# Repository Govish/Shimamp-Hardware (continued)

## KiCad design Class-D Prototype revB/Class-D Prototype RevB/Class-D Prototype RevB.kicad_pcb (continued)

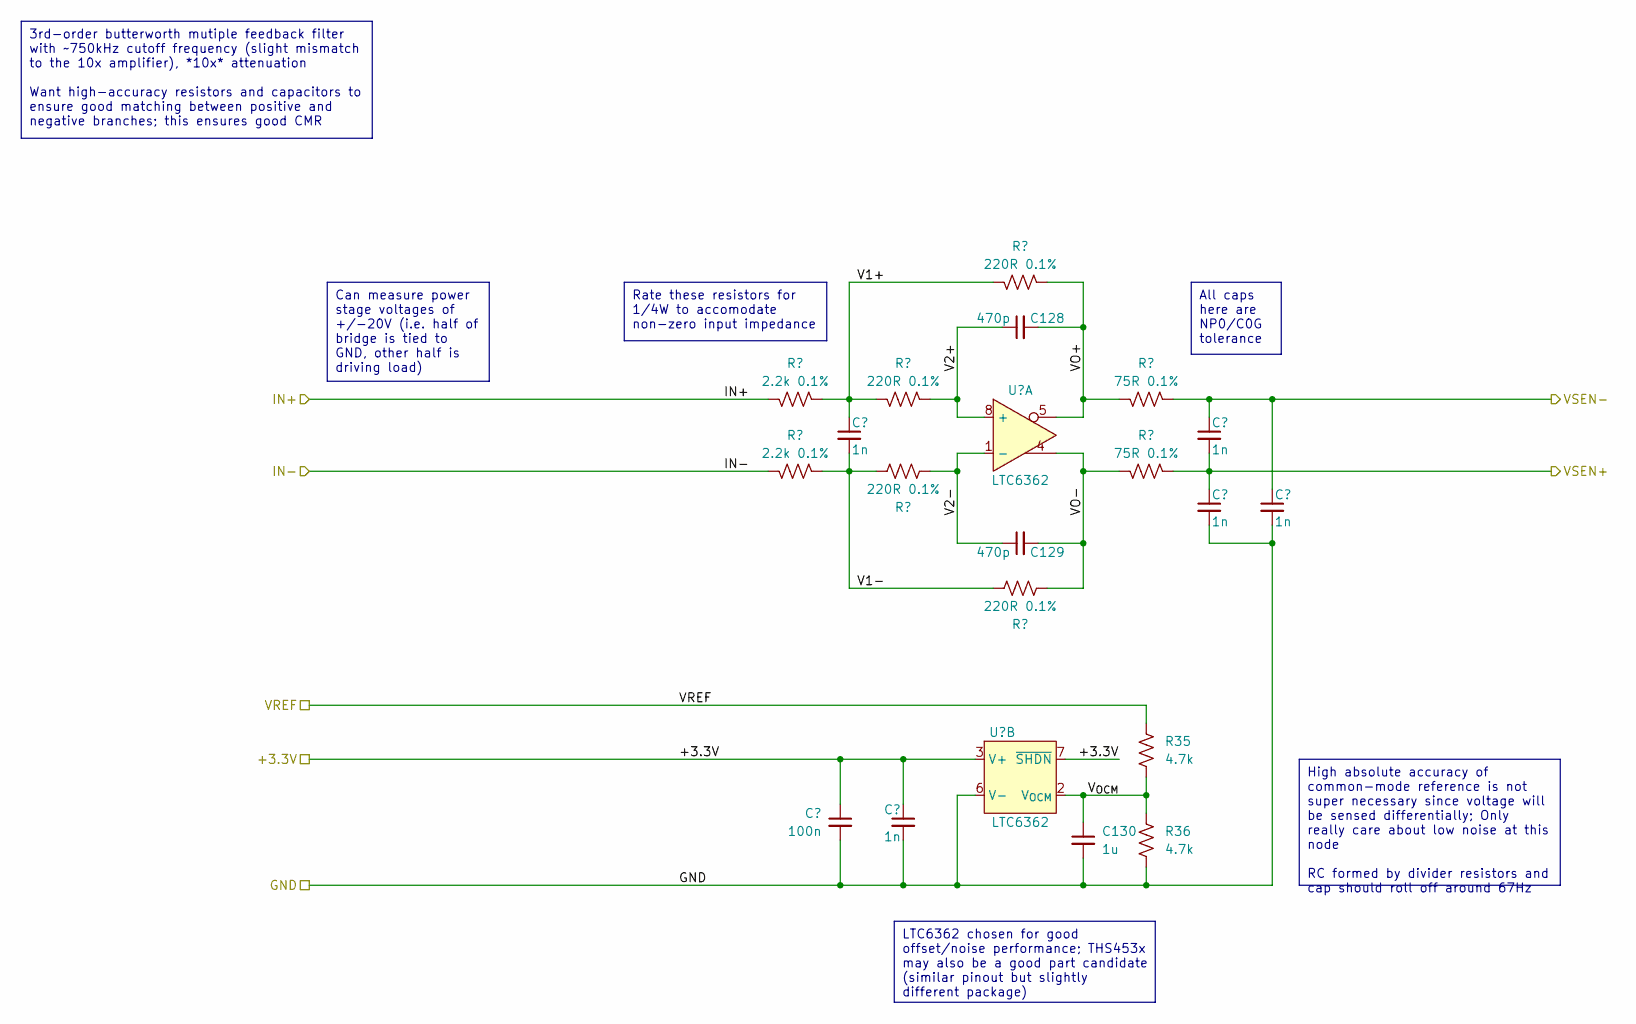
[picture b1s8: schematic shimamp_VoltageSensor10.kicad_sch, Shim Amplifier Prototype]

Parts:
C125: 100n; C_0603_1608Metric_Pad1.08x0.95mm_HandSolder; Part Number CL10B104KB8NNWC
C126, C127, C131, C132, C133: 1n; C_0603_1608Metric_Pad1.08x0.95mm_HandSolder; Part Number CL10B102KB8NNNC
C128, C129: 470p; C_0603_1608Metric_Pad1.08x0.95mm_HandSolder; Part Number GCM1885C2A471FA16D
C130: 1u; C_0805_2012Metric_Pad1.18x1.45mm_HandSolder; Part Number CL21B105KBFNNNG
R27, R28: 2.2k 0.1%; R_1206_3216Metric_Pad1.30x1.75mm_HandSolder; Part Number RN73R2BTTD2201B25
R29, R30, R31, R32: 220R 0.1%; R_0603_1608Metric_Pad0.98x0.95mm_HandSolder; Part Number RN73R1JTTD2200B25
R33, R34: 75R 0.1%; R_0603_1608Metric_Pad0.98x0.95mm_HandSolder; Part Number RN73R1JTTD75R0B25
R35, R36: 4.7k; R_0603_1608Metric_Pad0.98x0.95mm_HandSolder; Part Number RMCF0603FT4K70
U6: LTC6362; MSOP-8_3x3mm_P0.65mm; Part Number LTC6362CMS8#TRPBF

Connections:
+3.3V: C125.1, C127.1, U6.3 (V+), U6.7 (~SHDN); also elsewhere on the board
/Output Sensor/IN+: R27.2; also elsewhere on the board
/Output Sensor/IN-: R28.2; also elsewhere on the board
/Output Sensor/Voltage Sensor 10x/V1+: C126.1, R27.1, R29.2, R31.2
/Output Sensor/Voltage Sensor 10x/V1-: C126.2, R28.1, R30.2, R32.2
/Output Sensor/Voltage Sensor 10x/V2+: C128.1, R29.1, U6.8 (+)
/Output Sensor/Voltage Sensor 10x/V2-: C129.1, R30.1, U6.1 (-)
/Output Sensor/Voltage Sensor 10x/VO+: C128.2, R31.1, R33.2, U6.5
/Output Sensor/Voltage Sensor 10x/VO-: C129.2, R32.1, R34.2, U6.4
/Output Sensor/Voltage Sensor 10x/V_{OCM}: C130.1, R35.2, R36.1, U6.2 (V_{OCM})
/VSEN10x+: C131.2, C132.1, R34.1; also elsewhere on the board
/VSEN10x-: C131.1, C133.1, R33.1; also elsewhere on the board
GND: C125.2, C127.2, C130.2, C132.2, C133.2, R36.2, U6.6 (V-); also elsewhere on the board
V_{REF}: R35.1; also elsewhere on the board

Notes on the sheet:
LTC6362 chosen for good offset/noise performance; THS453x may also be a good part candidate (similar pinout but slightly different package)
3rd-order butterworth mutiple feedback filter with ~750kHz cutoff frequency (slight mismatch to the 10x amplifier), *10x* attenuation Want high-accuracy resistors and capacitors to ensure good matching between positive and negative branches; this ensures good CMR
All caps here are NP0/C0G tolerance
Rate these resistors for 1/4W to accomodate non-zero input impedance
Can measure power stage voltages of +/-20V (i.e. half of bridge is tied to GND, other half is driving load)
High absolute accuracy of common-mode reference is not super necessary since voltage will be sensed differentially; Only really care about low noise at this node RC formed by divider resistors and cap should roll off around 67Hz

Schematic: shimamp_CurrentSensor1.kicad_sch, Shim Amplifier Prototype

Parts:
C146, C148: 1n; C_0603_1608Metric_Pad1.08x0.95mm_HandSolder; Part Number CL10B102KB8NNNC
C147: 100n; C_0603_1608Metric_Pad1.08x0.95mm_HandSolder; Part Number CL10B104KB8NNWC
R48: 750R; R_0603_1608Metric_Pad0.98x0.95mm_HandSolder; Part Number RMCF0603FT750R
U9: INA241A1; SOT-23-8_Handsoldering; Part Number INA241A1IDDFR

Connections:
+3.3V: C147.1, U9.6 (VS); also elsewhere on the board
/ISEN1x: C148.1, R48.1; also elsewhere on the board
/Output Sensor/IS+: U9.8 (+); also elsewhere on the board
/Output Sensor/IS-: U9.1 (-); also elsewhere on the board
GND: C146.2, C147.2, C148.2, U9.2 (GND), U9.4 (GND), U9.7 (REF1); also elsewhere on the board
unnamed: R48.2, U9.5
V_{REF}: C146.1, U9.3 (REF2); also elsewhere on the board

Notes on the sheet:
Current sense is a single-ended measurement; filter rolls off ~212kHz
ADC range is from 0 to 2.048V--center the zero-current reading at 1.024V +/-10A thru 10mR with 10x gain should provide an output range of 0.024V to 2.024V
Reference divider is like insanely (ratiometrically) accurate, +/-0.005% maximum for the grade of part specified in this schematic; We'll never be able to easily generate something that accurate, so let's just leverage the chip's divider accuracy to generate the "zero-current reference voltage". Th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
Voltage reference can take a total of 10nF load capacitance at its output

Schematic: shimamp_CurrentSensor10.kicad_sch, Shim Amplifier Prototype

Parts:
C143, C145: 1n; C_0603_1608Metric_Pad1.08x0.95mm_HandSolder; Part Number CL10B102KB8NNNC
C144: 100n; C_0603_1608Metric_Pad1.08x0.95mm_HandSolder; Part Number CL10B104KB8NNWC
R47: 750R; R_0603_1608Metric_Pad0.98x0.95mm_HandSolder; Part Number RMCF0603FT750R
U8: INA241A4; SOT-23-8_Handsoldering; Part Number INA241A4IDDFR

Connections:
+3.3V: C144.1, U8.6 (VS); also elsewhere on the board
/ISEN10x: C145.1, R47.1; also elsewhere on the board
/Output Sensor/IS+: U8.8 (+); also elsewhere on the board
/Output Sensor/IS-: U8.1 (-); also elsewhere on the board
GND: C143.2, C144.2, C145.2, U8.2 (GND), U8.4 (GND), U8.7 (REF1); also elsewhere on the board
unnamed: R47.2, U8.5
V_{REF}: C143.1, U8.3 (REF2); also elsewhere on the board

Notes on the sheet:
Voltage reference can take a total of 10nF load capacitance at its output
Reference divider is like insanely (ratiometrically) accurate, +/-0.005% maximum for the grade of part specified in this schematic; We'll never be able to easily generate something that accurate, so let's just leverage the chip's divider accuracy to generate the "zero-current reference voltage". Th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
Current sense is a single-ended measurement; filter rolls off ~212kHz
ADC range is from 0 to 2.048V--center the zero-current reading at 1.024V +/-1A thru 10mR with 100x gain should provide an output range of 0.024V to 2.024V

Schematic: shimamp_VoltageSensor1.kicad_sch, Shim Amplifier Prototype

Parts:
C134: 100n; C_0603_1608Metric_Pad1.08x0.95mm_HandSolder; Part Number CL10B104KB8NNWC
C135: 150p; C_0603_1608Metric_Pad1.08x0.95mm_HandSolder; Part Number GCM1885C2A151JA16D
C136, C140, C141, C142: 1n; C_0603_1608Metric_Pad1.08x0.95mm_HandSolder; Part Number CL10B102KB8NNNC
C137, C138: 33p; C_0603_1608Metric_Pad1.08x0.95mm_HandSolder; Part Number GCM1885C2A330JA16D
C139: 1u; C_0805_2012Metric_Pad1.18x1.45mm_HandSolder; Part Number CL21B105KBFNNNG
R37, R38, R39, R40, R41, R42: 2.2k 0.1%; R_1206_3216Metric_Pad1.30x1.75mm_HandSolder; Part Number RN73R2BTTD2201B25
R43, R44: 75R 0.1%; R_0603_1608Metric_Pad0.98x0.95mm_HandSolder; Part Number RN73R1JTTD75R0B25
R45, R46: 4.7k; R_0603_1608Metric_Pad0.98x0.95mm_HandSolder; Part Number RMCF0603FT4K70
U7: LTC6362; MSOP-8_3x3mm_P0.65mm; Part Number LTC6362CMS8#TRPBF

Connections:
+3.3V: C134.1, C136.1, U7.3 (V+), U7.7 (~SHDN); also elsewhere on the board
/Output Sensor/IN+: R37.2; also elsewhere on the board
/Output Sensor/IN-: R38.2; also elsewhere on the board
/Output Sensor/Voltage Sensor 1x/V1+: C135.1, R37.1, R39.2, R41.2
/Output Sensor/Voltage Sensor 1x/V1-: C135.2, R38.1, R40.2, R42.2
/Output Sensor/Voltage Sensor 1x/V2+: C137.1, R39.1, U7.8 (+)
/Output Sensor/Voltage Sensor 1x/V2-: C138.1, R40.1, U7.1 (-)
/Output Sensor/Voltage Sensor 1x/VO+: C137.2, R41.1, R43.2, U7.5
/Output Sensor/Voltage Sensor 1x/VO-: C138.2, R42.1, R44.2, U7.4
/Output Sensor/Voltage Sensor 1x/V_{OCM}: C139.1, R45.2, R46.1, U7.2 (V_{OCM})
/VSEN1x+: C140.2, C141.1, R44.1; also elsewhere on the board
/VSEN1x-: C140.1, C142.1, R43.1; also elsewhere on the board
GND: C134.2, C136.2, C139.2, C141.2, C142.2, R46.2, U7.6 (V-); also elsewhere on the board
V_{REF}: R45.1; also elsewhere on the board

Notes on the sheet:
All caps here are NP0/C0G tolerance
LTC6362 chosen for good offset/noise performance; THS453x may also be a good part candidate (similar pinout but slightly different package)
Rate these resistors for 1/4W to accomodate non-zero input impedance
Can measure power stage voltages of +/-2V (i.e. half of bridge is tied to GND, other half is driving load) Amplifier inputs can be over-driven to +/-20V safely, though output will saturate
3rd-order butterworth mutiple feedback filter with ~730kHz cutoff frequency (slight mismatch to the 10x amplifier), *1x* attenuation Want high-accuracy resistors and capacitors to ensure good matching between positive and negative branches; this ensures good CMR
High absolute accuracy of common-mode reference is not super necessary since voltage will be sensed differentially; Only really care about low noise at this node RC formed by divider resistors and cap should roll off around 67Hz

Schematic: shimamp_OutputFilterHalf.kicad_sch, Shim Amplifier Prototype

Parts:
C69, C70: 330u; CP_Elec_10x12.6; Part Number 25SVPF330M
C71, C72, C73, C74, C75, C76, C78, C80, C82, C84: 22u; C_1210_3225Metric_Pad1.33x2.70mm_HandSolder; Part Number CL32B226KAJNNNE
C77, C86, C95, C96: 100n; C_0603_1608Metric_Pad1.08x0.95mm_HandSolder; Part Number CL10B104KB8NNWC
C79, C88: 10n; C_0603_1608Metric_Pad1.08x0.95mm_HandSolder; Part Number CL10B103KB8NNNC
C81, C90: 4.7n; C_0603_1608Metric_Pad1.08x0.95mm_HandSolder; Part Number CL10B472KB8NFNC
C83, C92: 1n; C_0603_1608Metric_Pad1.08x0.95mm_HandSolder; Part Number CL10B102KB8NNNC
C85, C87, C89, C91, C93, C94: 4.7u; C_0805_2012Metric_Pad1.18x1.45mm_HandSolder; Part Number CL21A475KLCLQNC
L2: 257n; COILCRAFT_2014; Part Number 2014VS-251MED
L3, L4: 90n; COILCRAFT_1212; Part Number 1212VS-90NMED
R22, R23: 2.2R; R_0805_2012Metric_Pad1.20x1.40mm_HandSolder; Part Number RPC0805JT2R20-UP
TP17, TP18, TP19, TP20, TP21, TP22: -; TestPoint_Pad_D2.0mm

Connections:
/Output Filter/Output Filter+/FILT_STG2: C69.1, C70.1, C71.1, C72.1, C73.1, C74.1, C75.1, C76.1, C78.1, C80.1, C82.1, C84.1, C85.1, C87.1, C89.1, C91.1, C93.1, C94.1, C95.1, C96.1, L2.1, L3.1, TP17.1
/Output Filter/Output Filter+/FILT_STG3: C77.1, C79.1, C81.1, C83.1, L3.2, L4.1, TP18.1
/Output Sensor/IN+: C86.1, C88.1, C90.1, C92.1, L4.2, TP19.1; also elsewhere on the board
/Power Stage/Power Stage Half Bridge+/SW: L2.2; also elsewhere on the board
GND: C69.2, C70.2, C71.2, C72.2, C73.2, C74.2, C75.2, C76.2, C78.2, C79.2, C80.2, C81.2, C82.2, C83.2, C84.2, C85.2, C87.2, C88.2, C89.2, C90.2, C91.2, C92.2, C93.2, C94.2, C95.2, C96.2, R22.2, R23.2, TP20.1, TP21.1, TP22.1; also elsewhere on the board
unnamed: C77.2, R22.1
unnamed: C86.2, R23.1

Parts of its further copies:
C97, C98: 330u; CP_Elec_10x12.6; Part Number 25SVPF330M
C99, C100, C101, C102, C103, C104, C106, C108, C110, C112: 22u; C_1210_3225Metric_Pad1.33x2.70mm_HandSolder; Part Number CL32B226KAJNNNE
C105, C114, C123, C124: 100n; C_0603_1608Metric_Pad1.08x0.95mm_HandSolder; Part Number CL10B104KB8NNWC
C107, C116: 10n; C_0603_1608Metric_Pad1.08x0.95mm_HandSolder; Part Number CL10B103KB8NNNC
C109, C118: 4.7n; C_0603_1608Metric_Pad1.08x0.95mm_HandSolder; Part Number CL10B472KB8NFNC
C111, C120: 1n; C_0603_1608Metric_Pad1.08x0.95mm_HandSolder; Part Number CL10B102KB8NNNC
C113, C115, C117, C119, C121, C122: 4.7u; C_0805_2012Metric_Pad1.18x1.45mm_HandSolder; Part Number CL21A475KLCLQNC
L5: 257n; COILCRAFT_2014; Part Number 2014VS-251MED
L6, L7: 90n; COILCRAFT_1212; Part Number 1212VS-90NMED
R24, R25: 2.2R; R_0805_2012Metric_Pad1.20x1.40mm_HandSolder; Part Number RPC0805JT2R20-UP
TP23, TP24, TP25, TP26, TP27, TP28: -; TestPoint_Pad_D2.0mm

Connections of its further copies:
/Output Filter/Output Filter-/FILT_STG2: C97.1, C98.1, C99.1, C100.1, C101.1, C102.1, C103.1, C104.1, C106.1, C108.1, C110.1, C112.1, C113.1, C115.1, C117.1, C119.1, C121.1, C122.1, C123.1, C124.1, L5.1, L6.1, TP23.1
/Output Filter/Output Filter-/FILT_STG3: C105.1, C107.1, C109.1, C111.1, L6.2, L7.1, TP24.1
/Output Sensor/IN-: C114.1, C116.1, C118.1, C120.1, L7.2, TP25.1; also elsewhere on the board
/Power Stage/Power Stage Half Bridge-/SW: L5.2; also elsewhere on the board
GND: C97.2, C98.2, C99.2, C100.2, C101.2, C102.2, C103.2, C104.2, C106.2, C107.2, C108.2, C109.2, C110.2, C111.2, C112.2, C113.2, C115.2, C116.2, C117.2, C118.2, C119.2, C120.2, C121.2, C122.2, C123.2, C124.2, R24.2, R25.2, TP26.1, TP27.1, TP28.1; also elsewhere on the board
unnamed: C105.2, R24.1
unnamed: C114.2, R25.1

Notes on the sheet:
Add a bit of damping to kill any peaks in the frequency response of the second and third stages
This is one half of a 3-stage, 6th-order filter that provides both differential and common-mode filtering. Since the control loop bandwidth is greater than the resonant frequency of the first filter stage, it can remain undamped. However, this is not the case with the second and third stages, requi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
Calculations for this filter (and control design) can be found under the 'simulations' folder in my Dropbox
- Aluminum Poly caps are good up to about ~2-300kHz - 22u ceramics are good to ~1MHz - 4.7u, 1u ceramics are good to ~8MHz - 100n ceramics are good to ~20MHz - 10n ceramics resonate at ~80MHz - 4.7n ceramics resonate at ~120MHz - 1n ceramics resonate at ~ 280MHz Ceramics will derate about 75% (i.e.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
Paralleled aluminum polymer capacitors for lower ESR and higher ripple rating; good for 100's of kHz; Inductor Ripple current ~4.75A worst case (50% duty cycle) with 12V supply, 1.25MHz switching; should result in <40mV ripple at the end of the first stage
In the board design, give the smallest capacitors the tightest loops; this will minimize parasitic inductance for those components where it matters most.

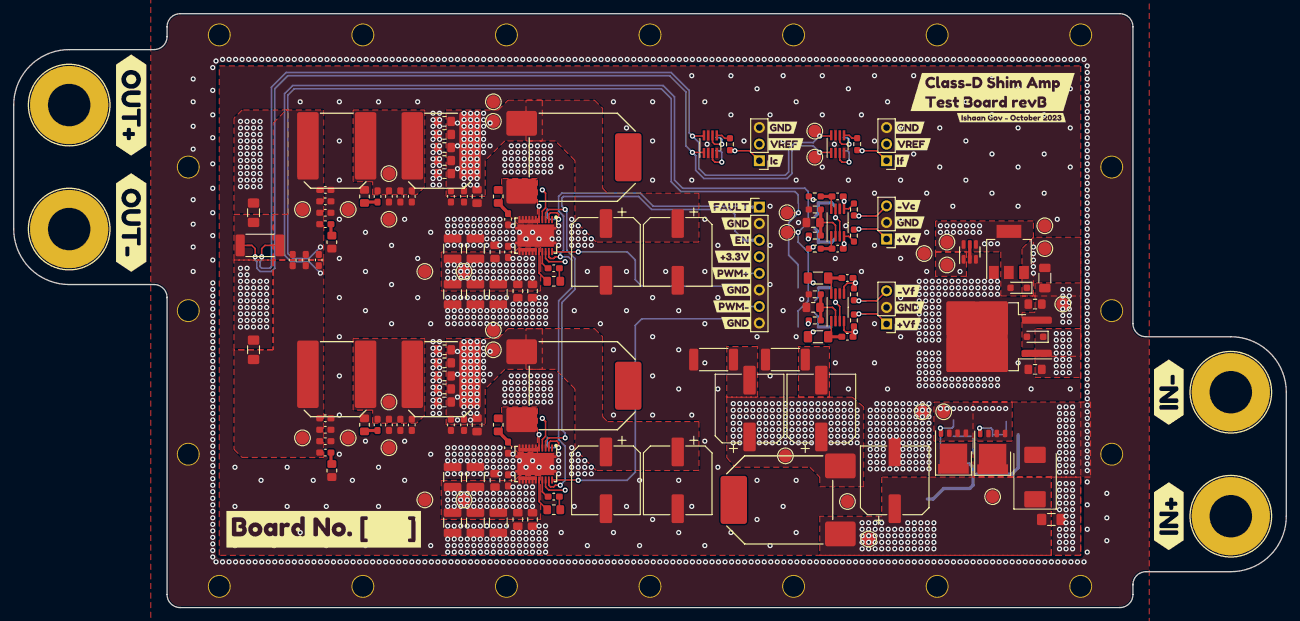
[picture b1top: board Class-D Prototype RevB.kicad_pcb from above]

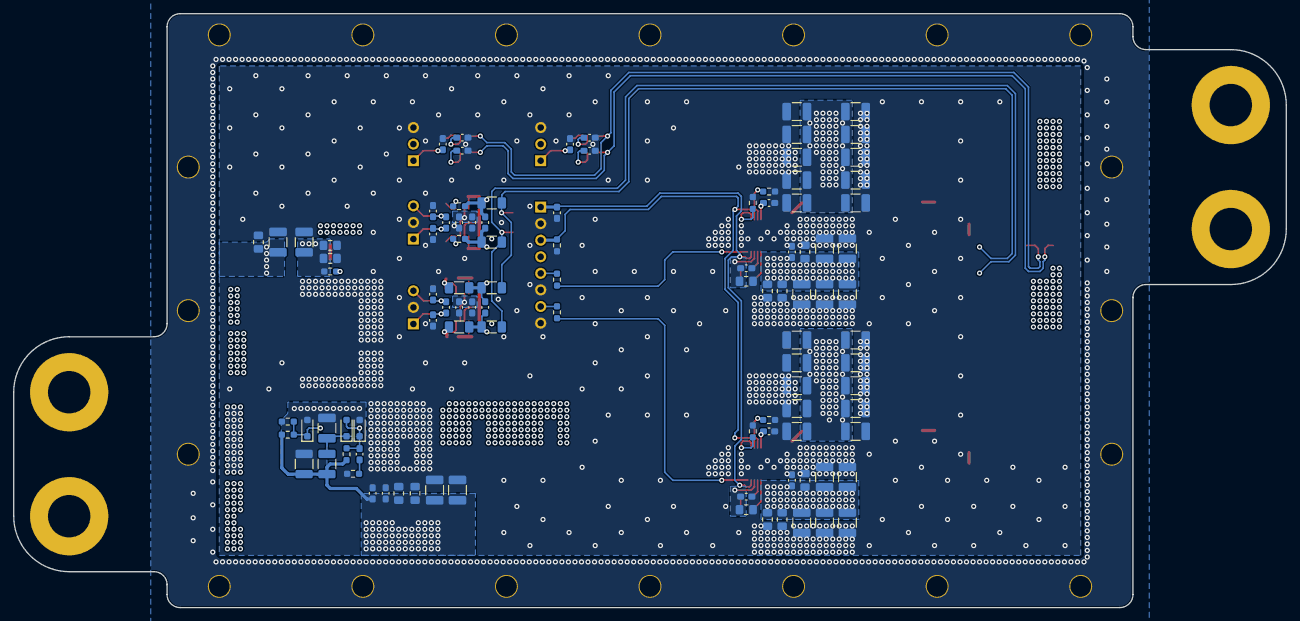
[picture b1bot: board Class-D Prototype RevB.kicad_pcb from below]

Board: 4 copper layers, 195.0 x 91.0 mm, 311 parts (101 on the bottom side), 73 nets.

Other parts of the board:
kibuzzard-6525E0C3: G***; kibuzzard-6525E0C3
kibuzzard-6525E1AD: G***; kibuzzard-6525E1AD
kibuzzard-6525E1B5: G***; kibuzzard-6525E1B5
kibuzzard-6525E1C4: G***; kibuzzard-6525E1C4
kibuzzard-6525E1D0: G***; kibuzzard-6525E1D0
kibuzzard-6525E1DB: G***; kibuzzard-6525E1DB
kibuzzard-6525E1FF: G***; kibuzzard-6525E1FF
kibuzzard-6525E2FE: G***; kibuzzard-6525E2FE
kibuzzard-6525E3DB: G***; kibuzzard-6525E3DB
kibuzzard-6525E19B: G***; kibuzzard-6525E19B
kibuzzard-6525E21C: G***; kibuzzard-6525E21C
kibuzzard-6525E23B: G***; kibuzzard-6525E23B
kibuzzard-6525E33F: G***; kibuzzard-6525E33F
kibuzzard-6525E43B: G***; kibuzzard-6525E43B
kibuzzard-6525E106: G***; kibuzzard-6525E106
kibuzzard-6525E114: G***; kibuzzard-6525E114
kibuzzard-6525E122: G***; kibuzzard-6525E122
kibuzzard-6525E130: G***; kibuzzard-6525E130
kibuzzard-6525E138: G***; kibuzzard-6525E138
kibuzzard-6525E140: G***; kibuzzard-6525E140
kibuzzard-6525E147: G***; kibuzzard-6525E147
kibuzzard-6525E213: G***; kibuzzard-6525E213
kibuzzard-6525E231: G***; kibuzzard-6525E231
kibuzzard-6525E244: G***; kibuzzard-6525E244
kibuzzard-6525E307: G***; kibuzzard-6525E307
kibuzzard-6525E349: G***; kibuzzard-6525E349
kibuzzard-6525E518: G***; kibuzzard-6525E518

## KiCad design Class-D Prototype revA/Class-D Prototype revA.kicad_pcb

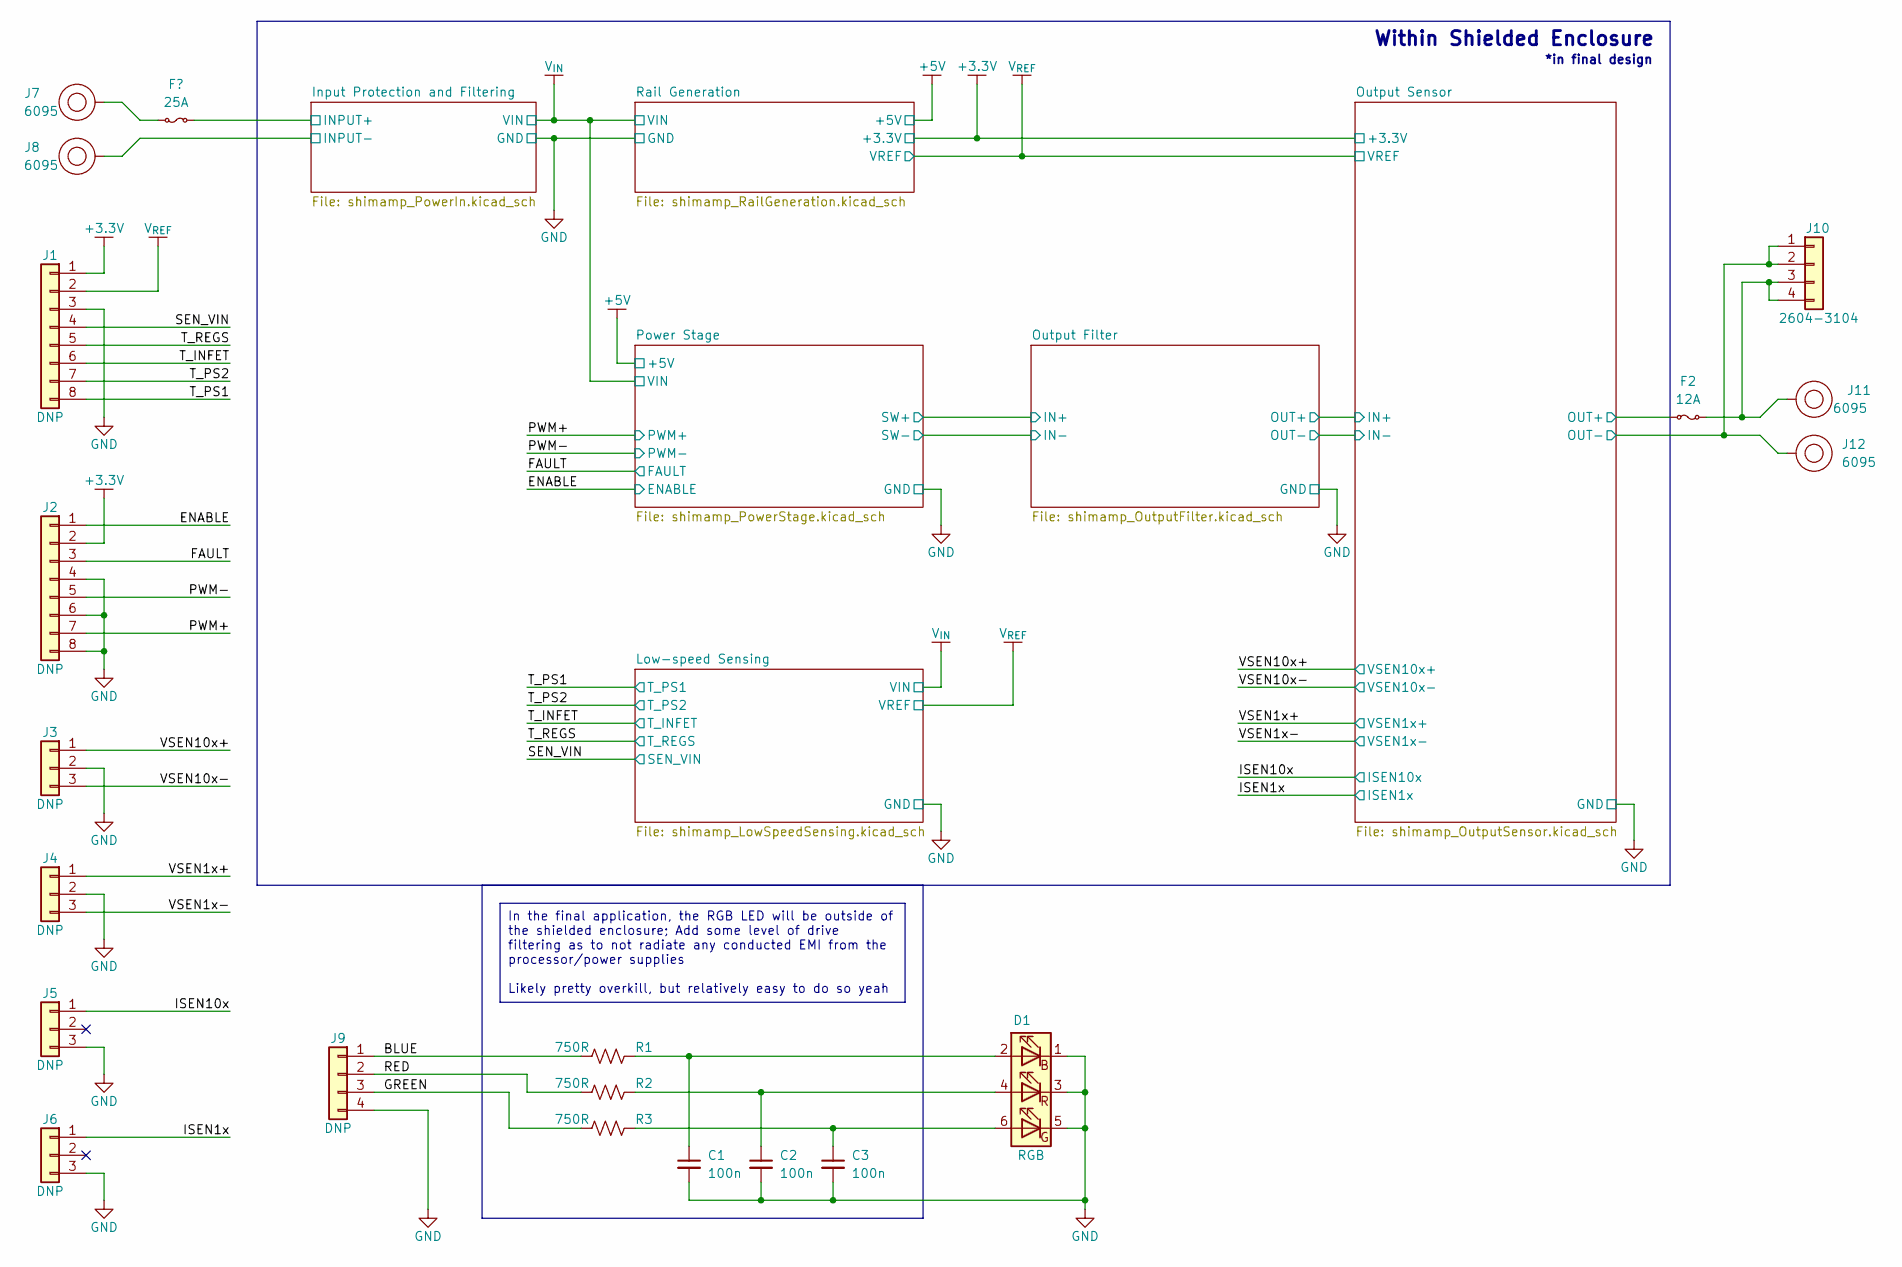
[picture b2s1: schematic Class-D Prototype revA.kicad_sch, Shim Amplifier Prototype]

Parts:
C1, C2, C3: 100n; C_0603_1608Metric_Pad1.08x0.95mm_HandSolder; Part Number CL10B104KB8NNWC
D1: RGB; LED_RGB_5050-6-WURTH; Part Number 150505M173300
F1: 25A; Fuse_1206_3216Metric_Pad1.42x1.75mm_HandSolder; Part Number 0685H9250-01
F2: 12A; Fuse_1206_3216Metric_Pad1.42x1.75mm_HandSolder; Part Number 0685H9120-01
J1, J2: DNP; PinHeader_1x08_P2.54mm_Vertical
J3, J4, J5, J6: DNP; PinHeader_1x03_P2.54mm_Vertical
J7, J8, J11, J12: 6095; Keystone 6095; Part Number 6095
J9: DNP; PinHeader_1x04_P2.54mm_Vertical
J10: 2604-3104; Wago_2604-3104; Part Number 2604-3104
R1, R2, R3: 750R; R_0603_1608Metric_Pad0.98x0.95mm_HandSolder; Part Number RMCF0603FT750R

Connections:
+3.3V: J1.1, J2.2; also elsewhere on the board
/BLUE: J9.1, R1.1
/ENABLE: J2.1; also elsewhere on the board
/FAULT: J2.3; also elsewhere on the board
/GREEN: J9.3, R3.1
/ISEN1x: J6.1; also elsewhere on the board
/ISEN10x: J5.1; also elsewhere on the board
/Input Protection and Filtering/INPUT-: J8.1; also elsewhere on the board
/Input Protection and Filtering/VIN_ICL+: F1.2; also elsewhere on the board
/Output Sensor/IN-: J10.1, J10.2, J12.1; also elsewhere on the board
/Output Sensor/OUT+: F2.1; also elsewhere on the board
/PWM+: J2.7; also elsewhere on the board
/PWM-: J2.5; also elsewhere on the board
/RED: J9.2, R2.1
/SEN_VIN: J1.4; also elsewhere on the board
/T_INFET: J1.6; also elsewhere on the board
/T_PS1: J1.8; also elsewhere on the board
/T_PS2: J1.7; also elsewhere on the board
/T_REGS: J1.5; also elsewhere on the board
/VSEN1x+: J4.1; also elsewhere on the board
/VSEN1x-: J4.3; also elsewhere on the board
/VSEN10x+: J3.1; also elsewhere on the board
/VSEN10x-: J3.3; also elsewhere on the board
GND: C1.2, C2.2, C3.2, D1.1 (BK), D1.3 (RK), D1.5 (GK), J1.3, J2.4, J2.6, J2.8, J3.2, J4.2, J5.3, J6.3, J9.4; also elsewhere on the board
unnamed: C1.1, D1.2 (BA), R1.2
unnamed: C3.1, D1.6 (GA), R3.2
unnamed: C2.1, D1.4 (RA), R2.2
unnamed: F1.1, J7.1
unnamed: F2.2, J10.3, J10.4, J11.1
V_{REF}: J1.2; also elsewhere on the board

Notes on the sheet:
In the final application, the RGB LED will be outside of the shielded enclosure; Add some level of drive filtering as to not radiate any conducted EMI from the processor/power supplies Likely pretty overkill, but relatively easy to do so yeah
*in final design
Within Shielded Enclosure

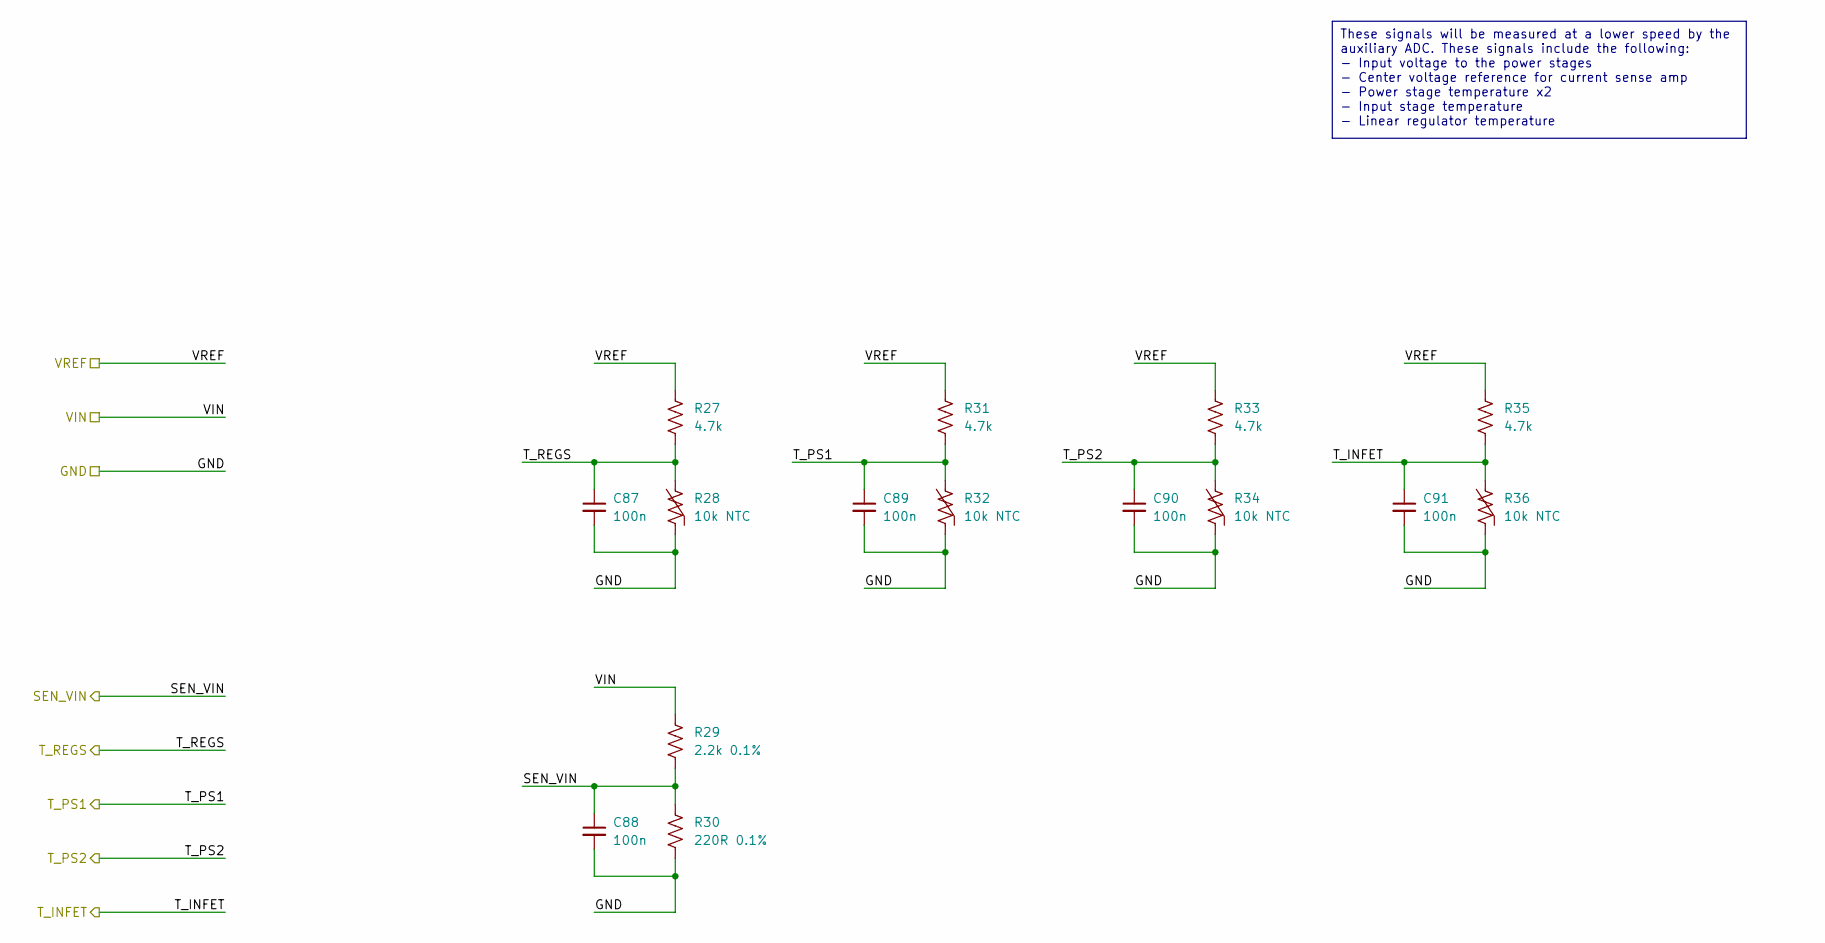
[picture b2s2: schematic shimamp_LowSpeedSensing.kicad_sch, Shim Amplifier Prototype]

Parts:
C87, C88, C89, C90, C91: 100n; C_0603_1608Metric_Pad1.08x0.95mm_HandSolder; Part Number CL10B104KB8NNWC
R27, R31, R33, R35: 4.7k; R_0603_1608Metric_Pad0.98x0.95mm_HandSolder; Part Number RMCF0603FT4K70
R28, R32, R34, R36: 10k NTC; R_0603_1608Metric_Pad0.98x0.95mm_HandSolder; Part Number B57330V2103F260
R29: 2.2k 0.1%; R_1206_3216Metric_Pad1.30x1.75mm_HandSolder; Part Number RN73R2BTTD2201B25
R30: 220R 0.1%; R_0603_1608Metric_Pad0.98x0.95mm_HandSolder; Part Number RN73R1JTTD2200B25

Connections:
/SEN_VIN: C88.1, R29.2, R30.1; also elsewhere on the board
/T_INFET: C91.1, R35.2, R36.1; also elsewhere on the board
/T_PS1: C89.1, R31.2, R32.1; also elsewhere on the board
/T_PS2: C90.1, R33.2, R34.1; also elsewhere on the board
/T_REGS: C87.1, R27.2, R28.1; also elsewhere on the board
GND: C87.2, C88.2, C89.2, C90.2, C91.2, R28.2, R30.2, R32.2, R34.2, R36.2; also elsewhere on the board
V_{IN}: R29.1; also elsewhere on the board
V_{REF}: R27.1, R31.1, R33.1, R35.1; also elsewhere on the board

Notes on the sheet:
These signals will be measured at a lower speed by the auxiliary ADC. These signals include the following: - Input voltage to the power stages - Center voltage reference for current sense amp - Power stage temperature x2 - Input stage temperature - Linear regulator temperature

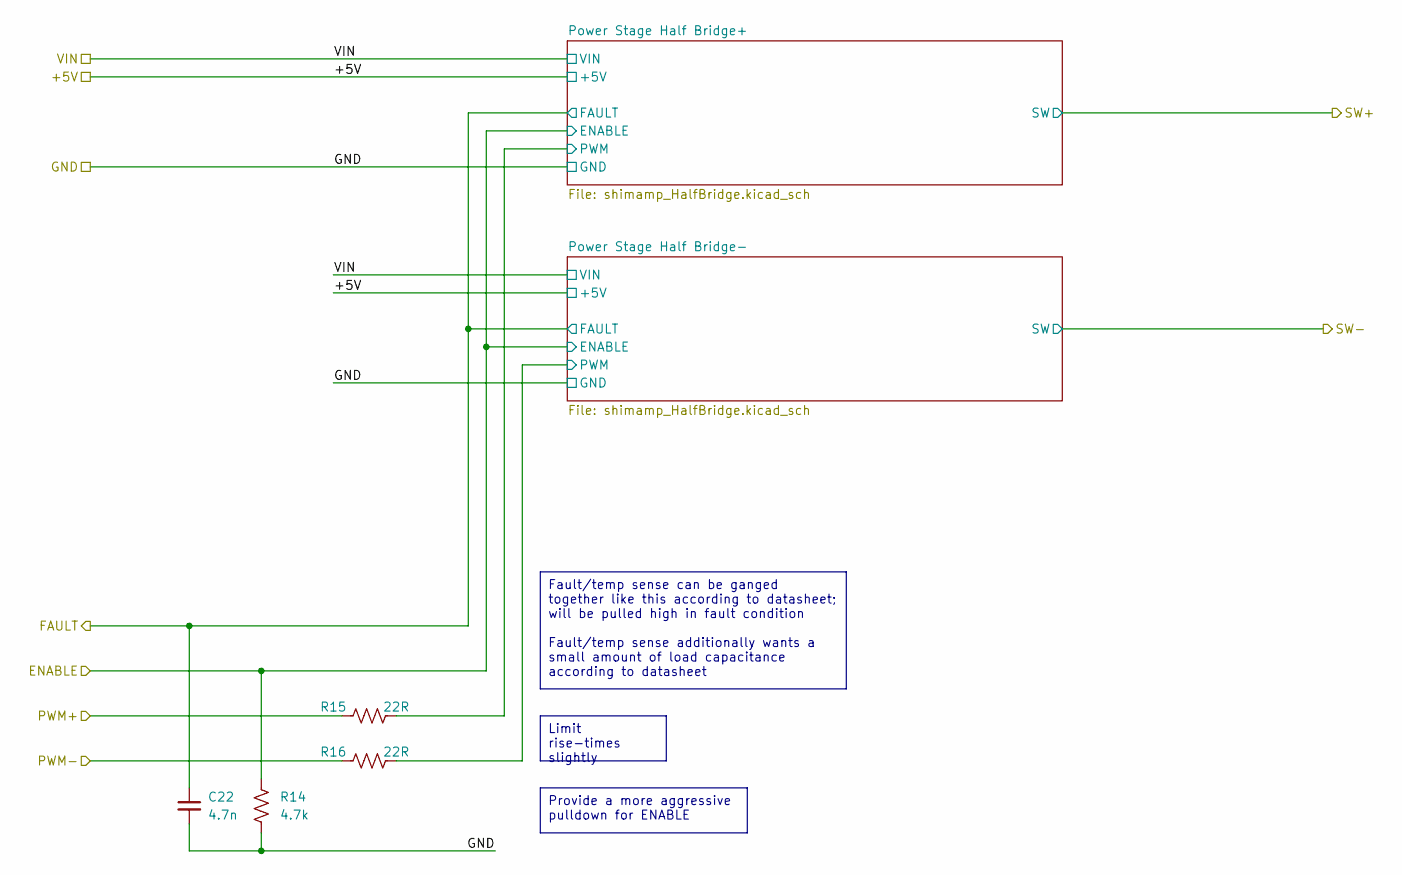
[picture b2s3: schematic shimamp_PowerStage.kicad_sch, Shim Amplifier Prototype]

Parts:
C22: 4.7n; C_0402_1005Metric_Pad0.74x0.62mm_HandSolder; Part Number CL05B472KB5NNNC
R14: 4.7k; R_0603_1608Metric_Pad0.98x0.95mm_HandSolder; Part Number RMCF0603FT4K70
R15, R16: 22R; R_0603_1608Metric_Pad0.98x0.95mm_HandSolder; Part Number RMCF0603FT22R0

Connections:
/ENABLE: R14.2; also elsewhere on the board
/FAULT: C22.1; also elsewhere on the board
/PWM+: R15.1; also elsewhere on the board
/PWM-: R16.1; also elsewhere on the board
/Power Stage/Power Stage Half Bridge+/PWM: R15.2; also elsewhere on the board
/Power Stage/Power Stage Half Bridge-/PWM: R16.2; also elsewhere on the board
GND: C22.2, R14.1; also elsewhere on the board

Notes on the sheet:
Limit rise-times slightly
Provide a more aggressive pulldown for ENABLE
Fault/temp sense can be ganged together like this according to datasheet; will be pulled high in fault condition Fault/temp sense additionally wants a small amount of load capacitance according to datasheet

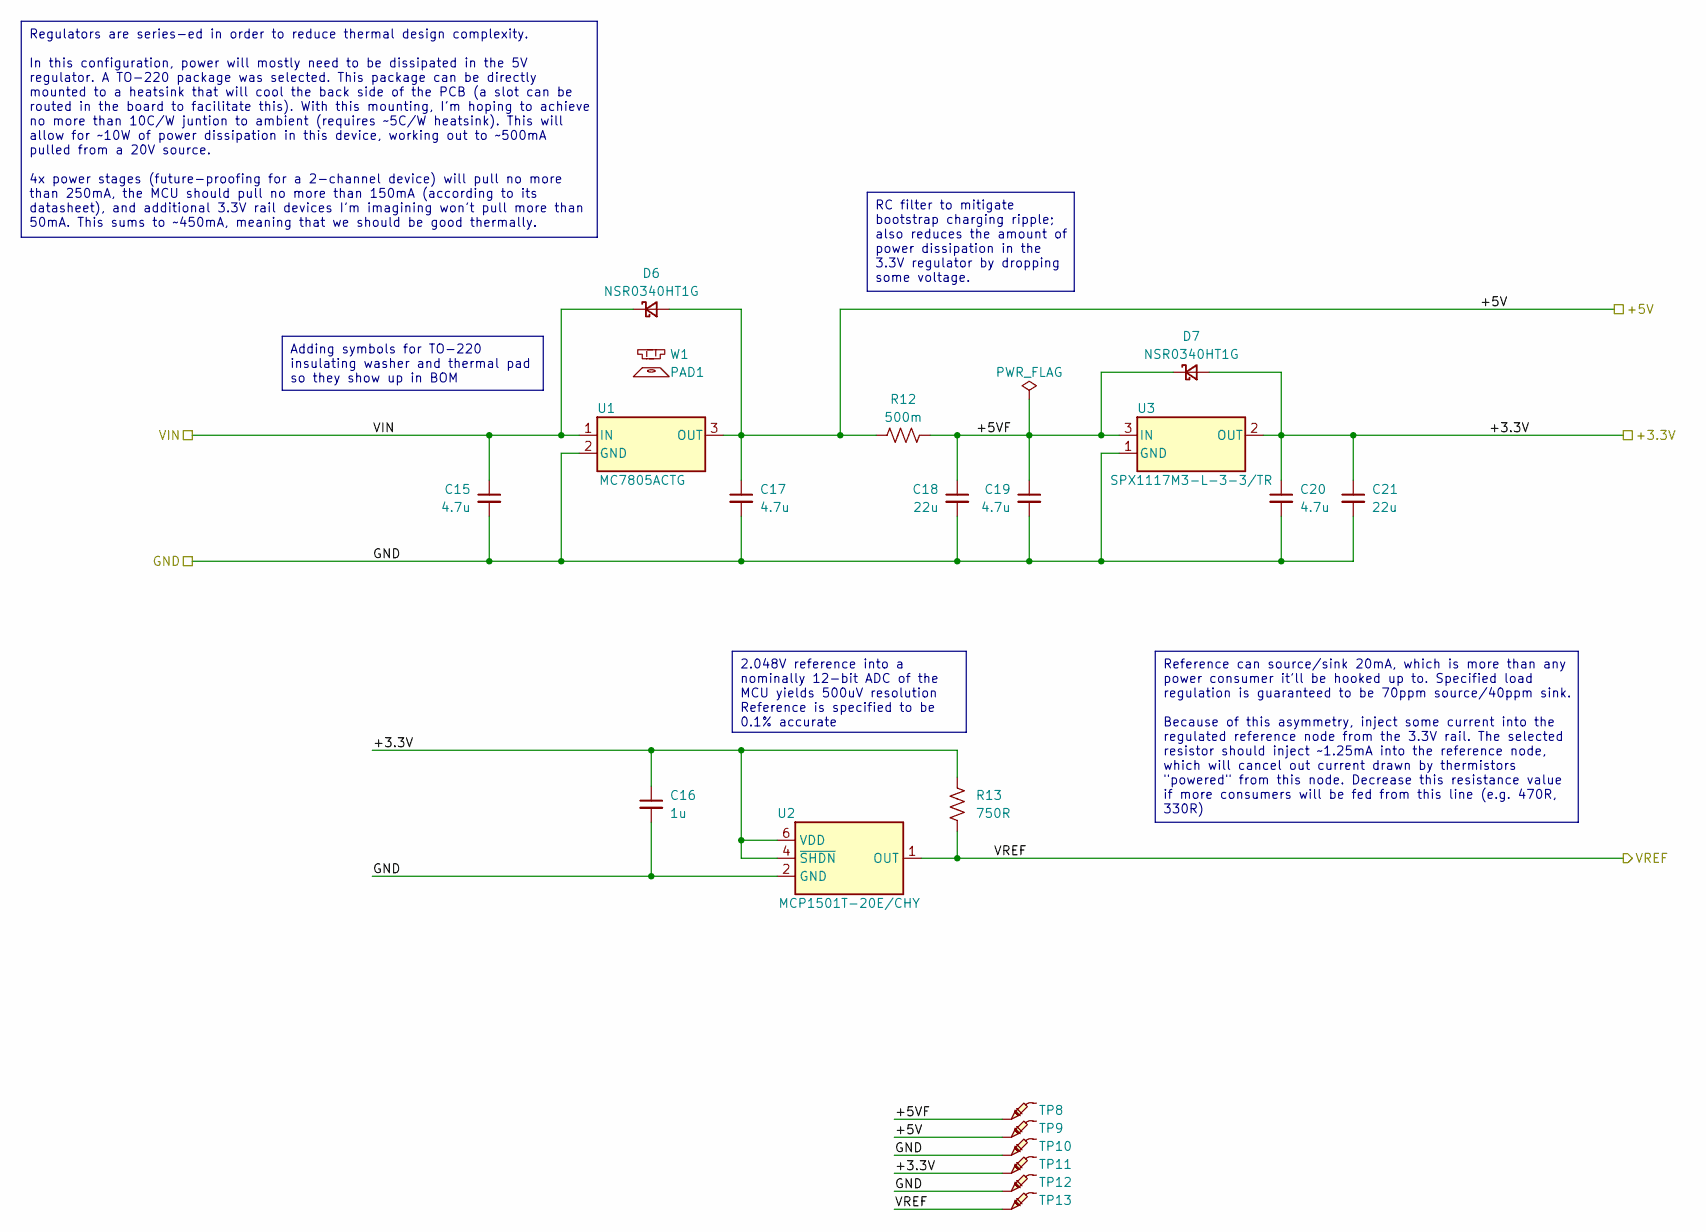
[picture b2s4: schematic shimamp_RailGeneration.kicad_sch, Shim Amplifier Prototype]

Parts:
C15, C17, C19, C20: 4.7u; C_0805_2012Metric_Pad1.18x1.45mm_HandSolder; Part Number CL21A475KLCLQNC
C16: 1u; C_0805_2012Metric_Pad1.18x1.45mm_HandSolder; Part Number CL21B105KBFNNNG
C18, C21: 22u; C_1210_3225Metric_Pad1.33x2.70mm_HandSolder; Part Number CL32B226KAJNNNE
D6, D7: NSR0340HT1G; D_SOD-323_HandSoldering; Part Number NSR0340HT1G
PAD1: 173-7-220P; Part Number 173-7-220P
R12: 500m; R_1206_3216Metric_Pad1.30x1.75mm_HandSolder; Part Number CSR1206FKR500
R13: 750R; R_0603_1608Metric_Pad0.98x0.95mm_HandSolder; Part Number RMCF0603FT750R
TP8, TP9, TP10, TP11, TP12, TP13: -; TestPoint_Pad_D2.0mm
U1: MC7805ACTG; TO-220-3_Horizontal_TabDown; Part Number MC7805ACTG
U2: MCP1501T-20E/CHY; SOT-23-6; Part Number MCP1501T-20E/CHY
U3: SPX1117M3-L-3-3/TR; SOT-223-3_TabPin2; Part Number SPX1117M3-L-3-3/TR
W1: INSULATING WASHER; Part Number V5359

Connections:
+3.3V: C16.1, C20.1, C21.1, D7.2 (A), R13.1, TP11.1, U2.4 (~SHDN), U2.6 (VDD), U3.2 (OUT); also elsewhere on the board
+5V: C17.1, D6.2 (A), R12.1, TP9.1, U1.3 (OUT); also elsewhere on the board
/Rail Generation/+5VF: C18.1, C19.1, D7.1 (K), R12.2, TP8.1, U3.3 (IN)
GND: C15.2, C16.2, C17.2, C18.2, C19.2, C20.2, C21.2, TP10.1, TP12.1, U1.2 (GND), U2.2 (GND), U2.3 (GND), U2.5 (GND), U3.1 (GND); also elsewhere on the board
V_{IN}: C15.1, D6.1 (K), U1.1 (IN); also elsewhere on the board
V_{REF}: R13.2, TP13.1, U2.1 (OUT); also elsewhere on the board

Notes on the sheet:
Regulators are series-ed in order to reduce thermal design complexity. In this configuration, power will mostly need to be dissipated in the 5V regulator. A TO-220 package was selected. This package can be directly mounted to a heatsink that will cool the back side of the PCB (a slot can be routed 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
2.048V reference into a nominally 12-bit ADC of the MCU yields 500uV resolution Reference is specified to be 0.1% accurate
Reference can source/sink 20mA, which is more than any power consumer it'll be hooked up to. Specified load regulation is guaranteed to be 70ppm source/40ppm sink. Because of this asymmetry, inject some current into the regulated reference node from the 3.3V rail. The selected resistor should injec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
Adding symbols for TO-220 insulating washer and thermal pad so they show up in BOM
RC filter to mitigate bootstrap charging ripple; also reduces the amount of power dissipation in the 3.3V regulator by dropping some voltage.
